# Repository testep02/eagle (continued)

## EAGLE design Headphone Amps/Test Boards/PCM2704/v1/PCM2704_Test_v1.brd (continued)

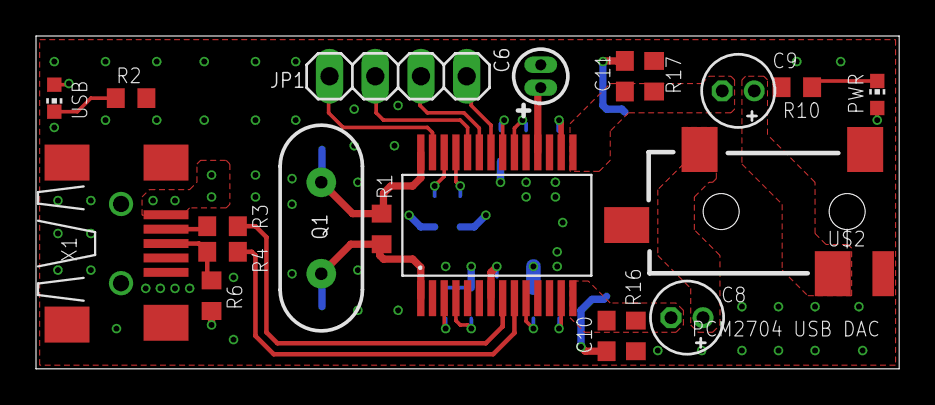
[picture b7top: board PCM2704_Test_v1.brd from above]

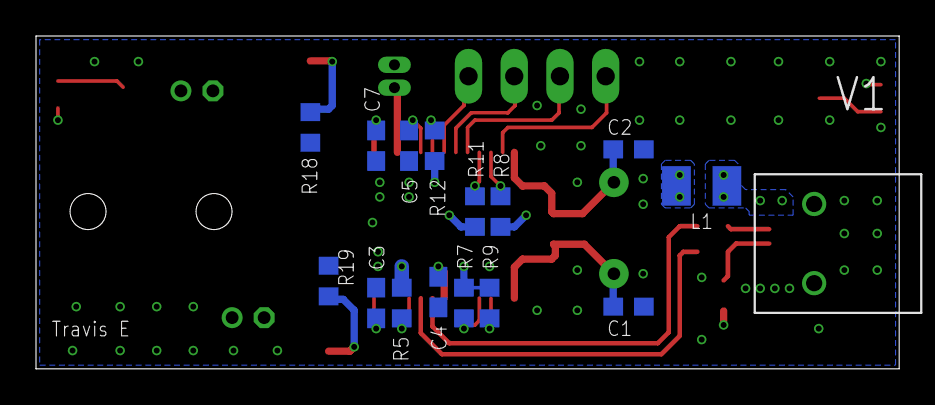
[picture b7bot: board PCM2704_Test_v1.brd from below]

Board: 4 copper layers, 48.0 x 18.5 mm, 35 parts (15 on the bottom side), 32 nets.
